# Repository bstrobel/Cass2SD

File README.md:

# Cass2SD - Cassettes to SD Cards - Kassetten zu SD-Karten

Replacement for cassette recorder by an SD card as mass storage device of old East-German 8-bit computers

Ersatz des Kassettenrekorders als Massenspeichergerät für DDR-Computer (KC85/2, KC85/3 und KC87, Z9001) durch eine SD-Karte

_The rest of the README and the Wiki is written in German since the audience of this tool is most probably mainly German speaking._

_Die Kommentare im Quellcode sind in Englisch gehalten, da ich das aus meinem Beruf so gewöhnt bin und sonst
den Text erst im Kopf ins Deutsche übersetzen müsste. Ich weiß, das klingt ein wenig affektiert, ist aber nicht
so gemeint._

## Eigenschaften und Ziele des Projekts

- Der alte Kassettenrecorder soll komplett ersetzt werden, ohne dass Veränderungen an den Computern vorgenommen werden müssen.
- Die Benutzeroberfläche soll einfach und bequem zu handhaben sein. Es sollen aber auch alle relevanten Funktionen und Informationen
  zur Verfügung stehen.
- Getestet wurde mit meinen beiden KCs, einem Z9001 (KC85/1.10) und einem KC85/3.
- Das Projekt wurde mit in meinem Bastelfundus vorhandenen Teilen umgesetzt, als da wären:
  - 8-bit Microcontroller ATMEL ATMega328P-PU
  - LCD 1602 (2 Zeilen zu 16 Zeichen mit HD44780-kompatiblem Controller)
  - LM358 Doppel-OPV für den Eingangsverstärker/Schmitt-Trigger
  - MicroSD Card Adapter für Arduino, welcher schon die notwendigen Pegelwandler von 3,3V auf 5V enthält, aber leider keine Erkennung,
  ob eine Karte gesteckt ist.
  - MCP1702-5002 Festspannungsregler im TO-92 Gehäuse
  - ALPS Drehimpulsgeber mit Taster in der Drehachse aus der EC11 Serie
- Als IDE habe ich AtmelStudio 7 und als Compiler den mitgelieferten avr-gcc genutzt.
- Programmiert und debugt habe ich den Atmel mit einem AVR Dragon.
- Programmiersprache ist C.
- Benutzte OpenSource-Bibliotheken - _meinen allerherzlichsten Dank an die Autoren, ohne deren Arbeit mein Projekt wohl nicht möglich gewesen wäre_:
  - Für die LCD-Anzeige-Routinen habe ich [die Bibliothek von Peter Fleury](http://homepage.hispeed.ch/peterfleury/avr-software.html#libs)  verwendet.
  - Für die FAT- und SD-Karten-SPI-Schnittstelle benutze ich die [FatFs-Bibliothek von Elm Chan](http://elm-chan.org/fsw/ff/00index_e.html)
- Was nicht geht:
  - Dateiliste sortieren. Der AVR hat einfach nicht genug Hauptspeicher dafür. Die Dateien werden genau in der
    Reihenfolge angezeigt, in der sie in der FAT gespeichert sind.
  - Verzeichnisse anlegen.
  - Dateien und Verzeichnisse löschen.  

## [Cass2SD Wiki](https://github.com/bstrobel/Cass2SD/wiki)

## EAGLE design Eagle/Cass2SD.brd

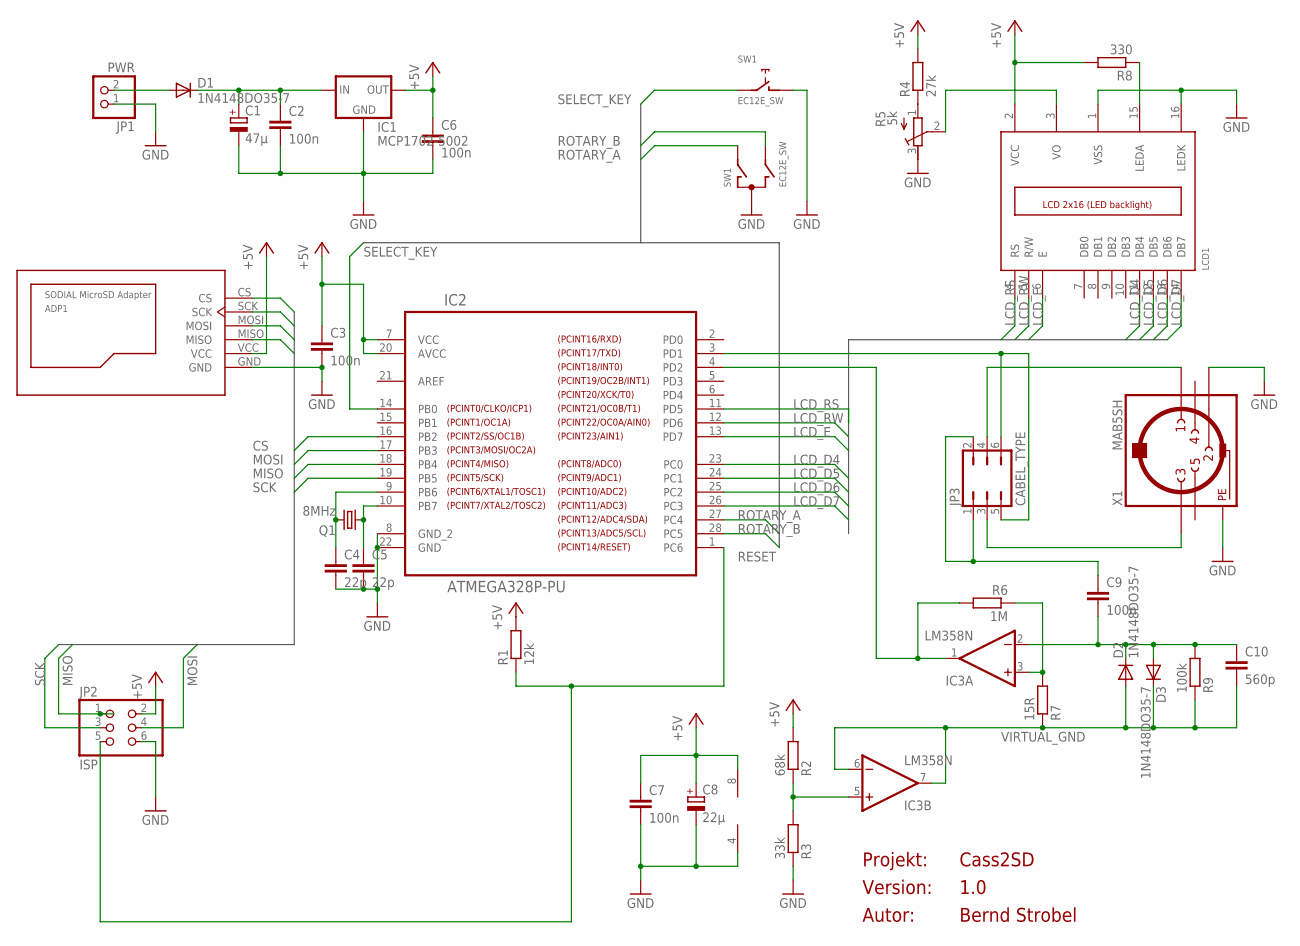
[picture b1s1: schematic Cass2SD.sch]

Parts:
ADP1: SODIAL_MICROSD_SPI_ADAPTER
C1: 47µ; E2,5-7
C2, C3, C6, C7, C9: 100n; C050-025X075
C4, C5: 22p; C050-025X075
C8: 22µ; E2,5-7
C10: 560p; C050-025X075
D1, D2, D3: 1N4148DO35-7; DO35-7
IC1: MCP1702-5002; TO92-
IC2: ATMEGA328P-PU; DIP254P762X457-28
IC3: LM358N; DIL08
JP1: PWR; 1X02
JP2: ISP; 2X03
JP3: CABEL_TYPE; JP3Q
LCD1: LCD_2X16; HY-1602F
Q1: 8MHz; HC49/S
R1: 12k; 0207/10
R2: 68k; 0207/10
R3: 33k; 0207/10
R4: 27k; 0207/10
R5: 5k; RTRIM64P
R6: 1M; 0207/10
R7: 15R; 0207/10
R8: 330; 0207/10
R9: 100k; 0207/10
SW1: EC12E_SW; ALPS_EC12E_SW
X1: MAB5SH

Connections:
+5V: ADP1.VCC, C3.1, C6.1, C7.1, C8.+, IC1.3 (OUT), IC2.7 (VCC), IC2.20 (AVCC), IC3.8 (V+), JP2.2, LCD1.2 (VCC), R1.2, R2.2, R4.2, R8.2
CS: ADP1.CS, IC2.16 (PB2)
GND: ADP1.GND, C1.-, C2.2, C3.2, C4.2, C5.2, C6.2, C7.2, C8.-, IC1.1 (GND), IC2.8 (GND_2), IC2.22 (GND), IC3.4 (V-), JP1.1, JP2.6, LCD1.1 (VSS), LCD1.16 (LEDK), R3.1, R5.3 (E), SW1.C, SW1.D (1), X1.2, X1.PE, X1.PE@ (PE)
LCD_D4: IC2.23 (PC0), LCD1.11 (DB4)
LCD_D5: IC2.24 (PC1), LCD1.12 (DB5)
LCD_D6: IC2.25 (PC2), LCD1.13 (DB6)
LCD_D7: IC2.26 (PC3), LCD1.14 (DB7)
LCD_E: IC2.13 (PD7), LCD1.6 (E)
LCD_RS: IC2.11 (PD5), LCD1.4 (RS)
LCD_RW: IC2.12 (PD6), LCD1.5 (R/W)
MISO: ADP1.MISO, IC2.18 (PB4), JP2.1
MOSI: ADP1.MOSI, IC2.17 (PB3), JP2.4
unnamed: C1.+, C2.1, D1.C, IC1.2 (IN)
unnamed: C9.2, C10.1, D2.C, D3.A, IC3.2 (-IN), R9.2
unnamed: IC3.5 (+IN), R2.1, R3.2
unnamed: C4.1, IC2.9 (PB6), Q1.2
unnamed: C5.1, IC2.10 (PB7), Q1.1
unnamed: C9.1, JP3.1, JP3.2
unnamed: IC3.3 (+IN), R6.1, R7.2
unnamed: IC2.4 (PD2), IC3.1 (OUT), R6.2
unnamed: D1.A, JP1.2
unnamed: IC2.3 (PD1), JP3.5, JP3.6
unnamed: LCD1.15 (LEDA), R8.1
unnamed: JP3.3, X1.3
unnamed: LCD1.3 (VO), R5.2 (S)
unnamed: R4.1, R5.1 (A)
unnamed: JP3.4, X1.1
RESET: IC2.1 (PC6), JP2.5, R1.1
ROTARY_A: IC2.27 (PC4), SW1.A
ROTARY_B: IC2.28 (PC5), SW1.B
SCK: ADP1.SCK, IC2.19 (PB5), JP2.3
SELECT_KEY: IC2.14 (PB0), SW1.E (2)
VIRTUAL_GND: C10.2, D2.A, D3.C, IC3.6 (-IN), IC3.7 (OUT), R7.1, R9.1

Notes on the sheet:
Projekt:
Version:
Autor:

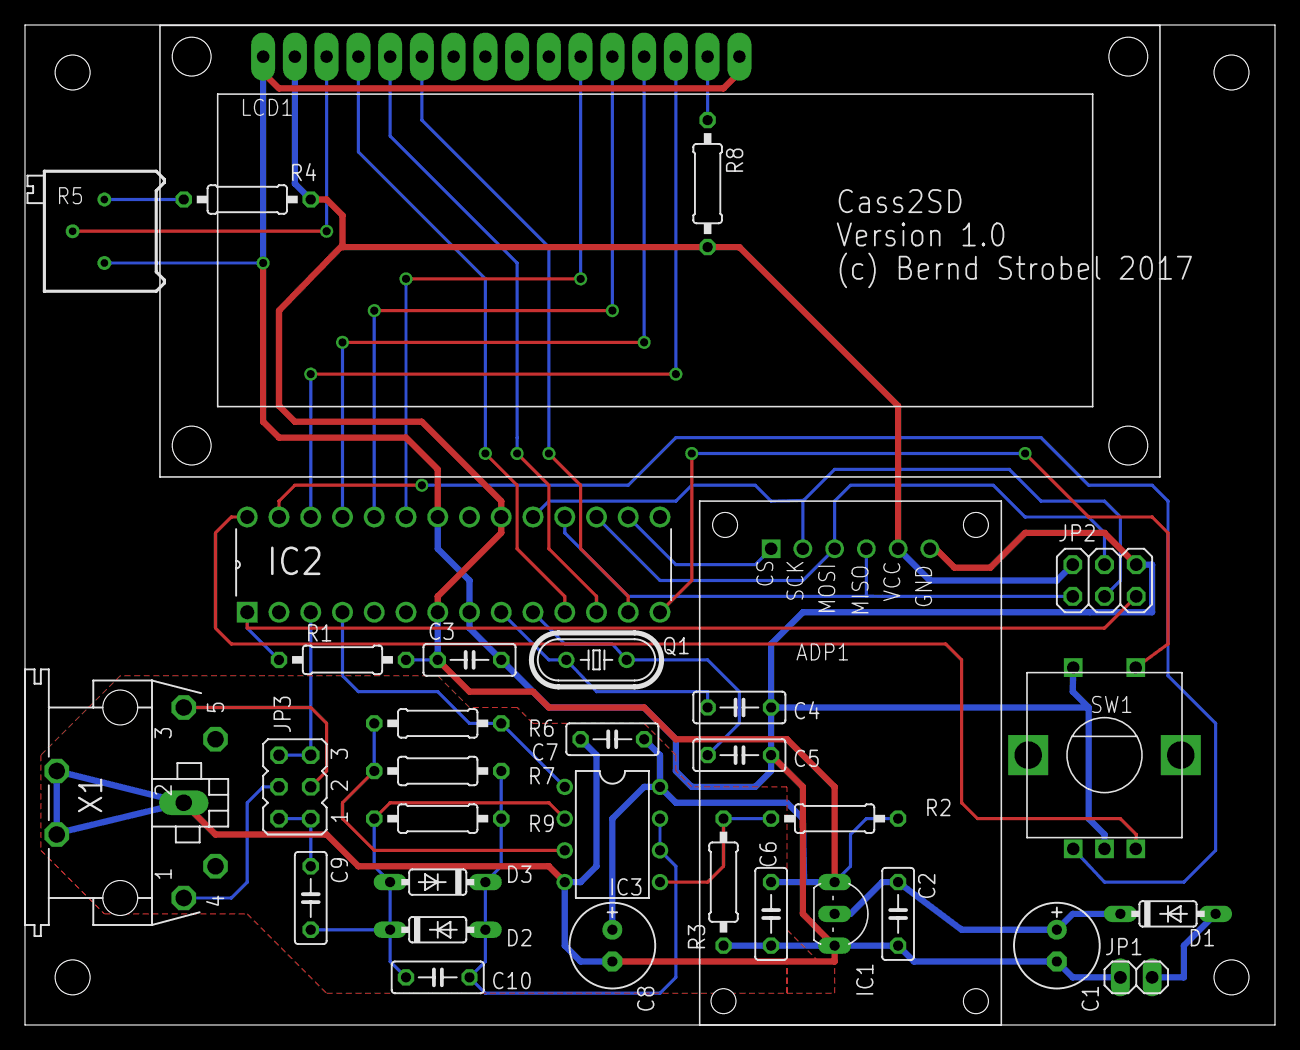
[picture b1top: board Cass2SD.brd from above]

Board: 2 copper layers, 100.0 x 80.0 mm, 33 parts (0 on the bottom side), 33 nets.

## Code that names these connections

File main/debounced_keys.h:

/*
 * debounced_keys.h
 *
 * Created: 02.12.2015 11:54:28
 *  Author: Bernd
 */ 


#ifndef DEBOUNCED_KEYS_H_
#define DEBOUNCED_KEYS_H_
#include <stdbool.h>

#ifndef DEBOUNCE_COUNTER_MAX
#	define DEBOUNCE_COUNTER_MAX 15U
#endif

#define PORT_ID_PORTA 0
#define PORT_ID_PORTB 1
#define PORT_ID_PORTC 2
#define PORT_ID_PORTD 3

#define NUM_KEYS 3

#define KEY_PIN_MAP { \
	{PORT_ID_PORTB, PINB0}, \
	{PORT_ID_PORTC, PINC4}, \
	{PORT_ID_PORTC, PINC5} \
}

extern void handle_keys(void);
extern void keys_init(void);

typedef enum {STAY=0, UP, DOWN} DIRECTION;

#define SELECT_KEY 0
#define ROTARY_A SELECT_KEY + 1
#define ROTARY_B ROTARY_A + 1

extern volatile DIRECTION display_task;
extern volatile bool select_key_pressed;
extern volatile bool select_key_changed;

#endif /* DEBOUNCED_KEYS_H_ */

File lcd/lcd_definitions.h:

/*
 * lcd_definitions.h
 *
 * Created: 4/24/2017 8:34:36 AM
 *  Author: Bernd
 */ 

 // This file will only be used if the symbol _LCD_DEFINITIONS_FILE is defined (i.e. -D_LCD_DEFINITIONS_FILE)!

#ifndef LCD_DEFINITIONS_H_
#define LCD_DEFINITIONS_H_

#define LCD_PORT         PORTC        /**< port for the LCD lines   */
#define LCD_DATA0_PORT   LCD_PORT     /**< port for 4bit data bit 0 */
#define LCD_DATA1_PORT   LCD_PORT     /**< port for 4bit data bit 1 */
#define LCD_DATA2_PORT   LCD_PORT     /**< port for 4bit data bit 2 */
#define LCD_DATA3_PORT   LCD_PORT     /**< port for 4bit data bit 3 */
#define LCD_DATA0_PIN    0            /**< pin for 4bit data bit 0  */
#define LCD_DATA1_PIN    1            /**< pin for 4bit data bit 1  */
#define LCD_DATA2_PIN    2            /**< pin for 4bit data bit 2  */
#define LCD_DATA3_PIN    3            /**< pin for 4bit data bit 3  */
#define LCD_RS_PORT      PORTD        /**< port for RS line         */
#define LCD_RS_PIN       5            /**< pin 11 for RS line         */
#define LCD_RW_PORT      PORTD        /**< port for RW line         */
#define LCD_RW_PIN       6            /**< pin 12 for RW line         */
#define LCD_E_PORT       PORTD        /**< port for Enable line     */
#define LCD_E_PIN        7            /**< pin 13 for Enable line     */

#endif /* LCD_DEFINITIONS_H_ */

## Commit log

2017-05-30 :lollipop: Added .gitattributes & .gitignore files
2017-05-30 First version working for MC in TAP files
2017-06-03 Directory navigation and menu items
2017-06-03 Refactored -> KC routiners in own files, DEBUG_TIMER
2017-06-03 Display routines moved into separate source files, more refactoring
2017-06-05 Refactoring, filetype handling, BASIC files not working
2017-06-06 More refactoring
2017-06-24 Send files works now for all file types
2017-06-25 Refactoring, Interrupt send
2017-06-25 Interrupt Send bug fixed
2017-06-25 VORTON based on current_block
2017-06-25 Initial implementation of receive code - NOT TESTED!
    ...so most probably not working yet.
2017-07-08 LTSpice Simulation of input circuit
2017-07-08 Many changes, recording not working yet
2017-07-08 LTSpice Simu input stage as schmitt trigger
2017-07-08 Input stage now with correct schmitt trigger
2017-07-09 File name detection during recieve not working yet
2017-07-09 Accidentally excluded
2017-07-17 Recording works for the first time!
2017-07-18 File receive works, SD Card SPI problem, Timer2 bug fixed
2017-07-19 Now saving correct TAP format
2017-07-20 Automatic send_file, display improvements
2017-07-22 volume information added, navigation improved
2017-07-22 Automatic display of file details
2017-07-22 send_file bug fixed
2017-07-22 Bug fix subdirectory display
2017-07-22 Memory optmization, display bugs fixed
2017-07-22 Next display bug fixed
2017-07-26 Saving files on KC85/3 fixed (long spaces), key debouncer optimized
2017-07-26 saving on KC85/3 fixed, display file info after record fixed
2017-07-26 Optimized display functions
2017-07-27 Completed main README
2017-07-27 README corrections
2017-07-27 Typos in README
2017-07-27 Removed unnecessary files
2017-07-27 Circuit schematics of cassette interfaces added
2017-07-27 Geracord circuit
2017-07-28 Timer1 init bug fixed, FCB generation for RAW fixed
2017-07-28 Handling of files without FCB improved
2017-07-28 Finally really fixed FCB check for non TAP files
2017-07-30 Bilder entfernt
2017-07-31 Readme updated
2017-08-07 Eagle files updated/added
2017-08-07 Eagle file cleanuup
2017-10-03 Changed to external XTAL with 16MHz
